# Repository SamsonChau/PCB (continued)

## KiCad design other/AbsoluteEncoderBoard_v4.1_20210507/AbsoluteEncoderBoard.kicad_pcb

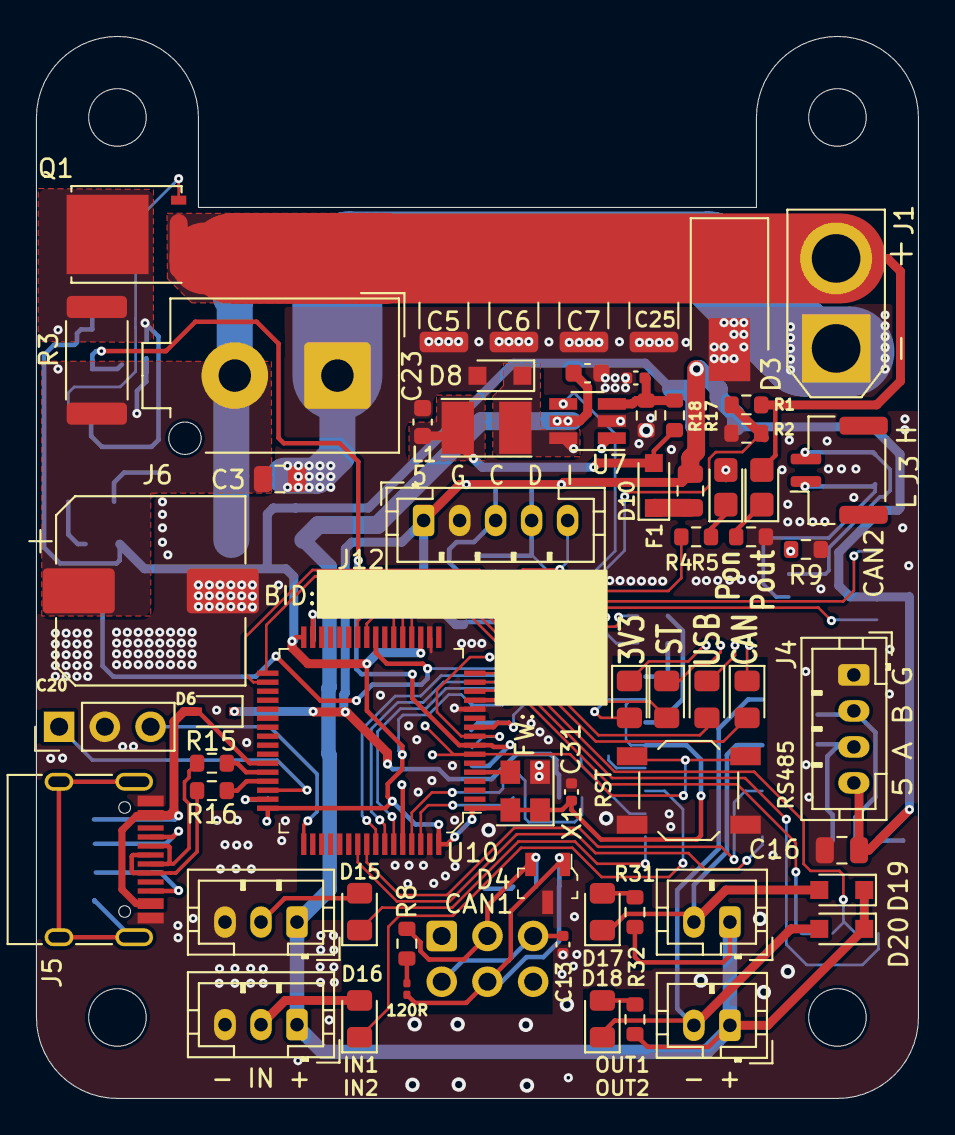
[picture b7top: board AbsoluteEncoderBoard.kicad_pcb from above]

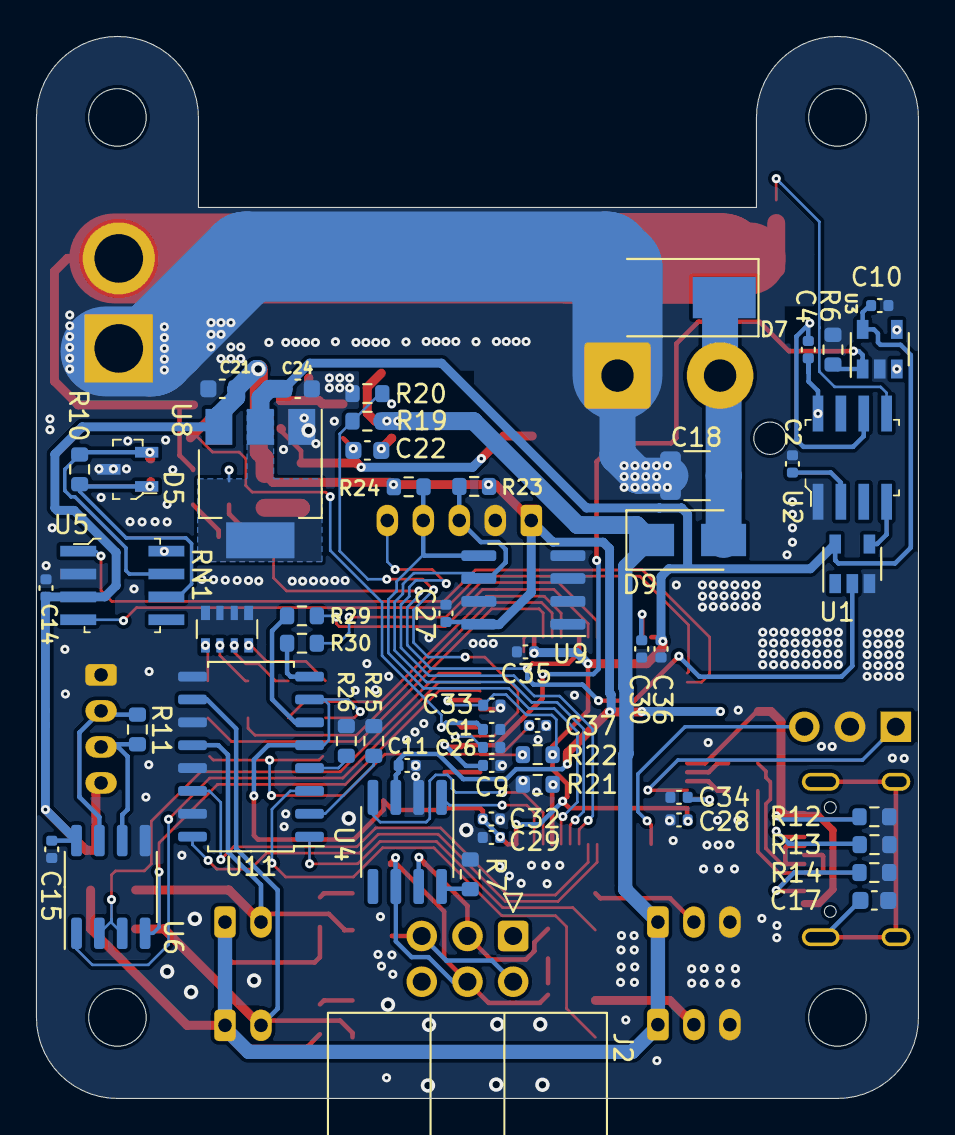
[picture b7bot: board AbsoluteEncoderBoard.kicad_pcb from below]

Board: 2 copper layers, 49.0 x 59.0 mm, 116 parts (55 on the bottom side), 79 nets.

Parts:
C1, C4, C9, C10, C11, C14, C15, C26, C27, C28, C29, C32, C33, C35, C36, C37: .1u; C_0402_1005Metric
C2: 10nF; C_0402_1005Metric
C3: 22u 50V; C_0805_2012Metric
C5, C6, C7, C8: 100u; C_1210_3225Metric
C13, C25: 30p; C_0402_1005Metric
C16: 22u; C_0805_2012Metric
C17: 30p; C_0603_1608Metric
C18: 100uF; C_1210_3225Metric
C19, C23: 10u; C_0603_1608Metric
C20: 330u; CP_Elec_10x10
C21, C24: 1u; C_0603_1608Metric
C22: .1u; C_0603_1608Metric
C30, C34: 2.2u; C_0402_1005Metric
C31: 0.01u; C_0402_1005Metric
D1: G; LED_0805_2012Metric_Castellated
D2: R; LED_0805_2012Metric_Castellated
D3: SMBJ30CA; D_SMB_Handsoldering
D4, D5: PESD1CAN_215; SOT-23-3
D6: N/A; D_SOD-323
D7: SMBJ24CA; D_SMB_Handsoldering
D8, D10, D19, D20: 1N5819; D_SOD-323_HandSoldering
D9: SS24; D_SMA
D11, D15, D16, D17, D18: G; LED_0805_2012Metric_Pad1.15x1.40mm_HandSolder
D12: R; LED_0805_2012Metric_Pad1.15x1.40mm_HandSolder
D13: B; LED_0805_2012Metric_Pad1.15x1.40mm_HandSolder
D14: Y; LED_0805_2012Metric_Pad1.15x1.40mm_HandSolder
F1: .5A; Fuse_0805_2012Metric
J1: XT30-F; AMASS_XT30U-F_1x02_P5.0mm_Vertical
J2: IDC_6P; IDC-Header_2x03_P2.54mm_Horizontal_Lock
J3: JST_GH_2P_HORZ; JST_GH_SM02B-GHS-TB_1x02-1MP_P1.25mm_Horizontal
J4: CONN_04JST-PTH; JST_PH_B4B-PH-K_1x04_P2.00mm_Vertical
J5: USB_C_M12; USB_C_Receptacle_HRO_TYPE-C-31-M-12
J6: MegaFit; Molex_Mega-Fit_76829-0102_2x01_P5.70mm_Vertical
J7: HDR_3P_Hor; PinHeader_1x03_P2.54mm_Vertical
J8, J9: JST_PH3; JST_PH_B3B-PH-K_1x03_P2.00mm_Vertical
J10, J11: JST_PH2; JST_PH_B2B-PH-K_1x02_P2.00mm_Vertical
J12: PH_5P; JST_PH_B5B-PH-K_1x05_P2.00mm_Vertical
L1: 3.3uH; L_Taiyo-Yuden_NR-30xx_HandSoldering
Q1: NVMFS5C450; TDSON-8-1
R1, R19: 27K; R_0603_1608Metric
R2, R4, R7, R9, R21: 2K; R_0603_1608Metric
R3: .002R; R_2512_6332Metric
R5, R12, R18, R22, R23, R24, R25, R26, R31, R32: 22K; R_0603_1608Metric
R6: 330K; R_0603_1608Metric
R8, R10, R11: 120R; R_0603_1608Metric
R13, R14: 5.1K; R_0603_1608Metric
R15, R16: 22R; R_0603_1608Metric
R17: 124K; R_0603_1608Metric
R20: 2K2; R_0603_1608Metric
R27: 0R/NA; R_0201_0603Metric
R29, R30: 100R; R_0603_1608Metric
RN1: 1K; R_Array_Convex_4x0603
SW1: SW_Push; SW_SPST_TL3342
U1: SN74LVC1G14DBV; SOT-23-5
U2: LT1910E; SOIC-8_W3.9mm
U3: INA138; SOT-23-5
U4: MCP2551-I-SN; SOIC-8_3.9x4.9mm_P1.27mm
U5: MCP2551; SOIC-8_W3.9mm
U6: MAX485E; SO-8_3.9x4.9mm_P1.27mm
U7: MP2451; SOT-23-6_Handsoldering
U8: AMS1117-3.3; SOT-223-3_TabPin2
U9: AT24CS64-SSHM; SOIC-8_3.9x4.9mm_P1.27mm
U10: STM32F405RGT6; LQFP-64_10x10mm
U11: TLP291-4; SOIC-16_4.55x10.3mm_P1.27mm
X1: ASE-12MHz; Oscillator_SMD_Abracon_ASE-4Pin_3.2x2.5mm

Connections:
+3V3: C10.1, C24.1, C28.1, C29.1, C31.1, C32.1, C33.1, C35.1, C36.1, D1.2, D11.2, R22.2, U1.5, U3.5, U8.2, U10.1, U10.13, U10.19, U10.32, U10.48, U10.64, U11.5, U11.7, X1.1, X1.4
+5V: C11.1, C14.2, C15.1, C16.1, C21.1, C27.1, D6.1, F1.1, J4.4, J12.1, R23.1, R24.1, U4.3, U5.3, U6.8, U8.3, U9.8
+24V: C19.1, D9.1, D19.1, D20.1, J8.1, J9.1, J10.1, J11.1, R19.2, R31.1, R32.1, U7.5
+BATT: C3.1, C4.1, C18.1, C20.1, D7.1, D9.2, J6.2, R3.1, U2.8, U3.3
/CAN1/CANH: D4.2, J2.3, R8.1, U4.7
/CAN1/CANL: D4.1, J2.4, R27.2, U4.6
/CAN1/SH: C13.1, J2.2, J2.5
/CAN1_RX: U4.4, U10.61
/CAN1_TX: U4.1, U10.62
/CAN2/CAN+: D5.2, J3.2, R10.1, U5.7
/CAN2/CAN-: D5.1, J3.1, R10.2, U5.6
/CAN2_RX: U5.4, U10.33
/CAN2_TX: U5.1, U10.34
/IN1: U10.55, U11.16
/IN2: U10.56, U11.14
/I_SEN: C9.1, R6.2, U3.1, U10.8
/MCU/BOOT0: R21.2, U10.60
/MCU/I2C1_INT: J12.5, U10.57
/MCU/LED1: D12.2, U10.22
/MCU/LED2: D13.2, U10.21
/MCU/LED3: D14.2, U10.20
/MCU/NRST: C37.2, R22.1, SW1.2, U10.7
/MCU/RCC_OSC_IN: U10.5, X1.3
/MCU/SYS_SWCLK: J7.3, U10.49
/MCU/SYS_SWDIO: J7.1, U10.46
/MCU/USB_DM: R15.1, U10.44
/MCU/USB_DP: R16.1, U10.45
/MCU/VCAP1: C30.1, U10.31
/MCU/VCAP2: C34.1, U10.47
/OUT1: R29.2, U10.25
/OUT2: R30.2, U10.26
/PWR_ON: R4.1, U1.2, U10.24
/RS485/RS485_N: J4.2, R11.2, U6.7
/RS485/RS485_P: J4.3, R11.1, U6.6
/RS485_RX: U6.1, U10.15
/RS485_TX: U6.4, U10.14
/RS485_TXEN: U6.2, U6.3, U10.16
/SCL: J12.3, R23.2, U9.6, U10.58
/SDA: J12.4, R24.2, U9.5, U10.59
/USB/USBD+: J5.A6, J5.B6, R16.2
/USB/USBD-: J5.A7, J5.B7, R15.2
/USB/VBUS: D6.2, J5.A4, J5.A9, J5.B4, J5.B9, R12.1, U10.43
/VIN_SEN: C26.1, R19.1, R20.2, U7.4, U10.9
/VOUT_SEN: C1.1, R1.1, R2.2, U10.10
/VoltageReg/FB: C25.2, R17.1, R18.2, U7.3
/dji_power/GATE: Q1.4, U2.5
/dji_power/I_SENSE-: C4.2, Q1.5, R3.2, U2.6, U3.4
/dji_power/M_ON: U1.4, U2.4
GND: C1.2, C2.2, C3.2, C5.2, C6.2, C7.2, C8.2, C9.2, C10.2, C11.2, C13.2, C14.1, C15.2, C16.2, C17.1, C18.2, C19.2, C20.2, C21.2, C23.1, C24.2, C25.1, C26.2, C27.2, C28.2, C29.2, C30.2, C31.2, C32.2, C33.2, C34.2, C35.2, C36.2, C37.1, D3.2, D4.3, D5.3, D7.2, D8.2, J1.1, J4.1, J5.A1, J5.A12, J5.B1, J5.B12, J6.1, J7.2, J8.3, J9.3, J12.2, R2.1, R5.1, R6.1, R7.1, R9.1, R12.2, R13.1, R14.1, R18.1, R20.1, R21.1, R25.2, R26.2, RN1.1, RN1.2, RN1.3, RN1.4, SW1.1, U1.3, U2.1, U3.2, U4.2, U5.2, U6.5, U7.2, U8.1, U9.1, U9.2, U9.3, U9.4, U9.7, U10.12, U10.18, U10.63, U11.9, U11.11, U11.13, U11.15, X1.2
unnamed: C2.1, U2.2
unnamed: C17.2, J5.S1
unnamed: C22.1, D8.1, L1.1, U7.6
unnamed: C22.2, U7.1
unnamed: C23.2, D10.2, L1.2, R17.2
unnamed: D1.1, R4.2
unnamed: D2.1, R5.2
unnamed: D10.1, F1.2
unnamed: D11.1, RN1.8
unnamed: D12.1, RN1.7
unnamed: D13.1, RN1.6
unnamed: D14.1, RN1.5
unnamed: D15.1, U11.1
unnamed: D15.2, J8.2
unnamed: D16.1, U11.3
unnamed: D16.2, J9.2
unnamed: D17.1, D19.2, J10.2, U11.12
unnamed: D17.2, R31.2
unnamed: D18.1, D20.2, J11.2, U11.10
unnamed: D18.2, R32.2
unnamed: J5.A5, R13.2
unnamed: J5.B5, R14.2
unnamed: R7.2, U4.8
unnamed: R9.2, U5.8
unnamed: R25.1, U11.2
unnamed: R26.1, U11.4
unnamed: R8.2, R27.1
unnamed: R29.1, U11.6
unnamed: R30.1, U11.8
Vdrive: C5.1, C6.1, C7.1, C8.1, D2.2, D3.1, J1.2, Q1.1, Q1.2, Q1.3, R1.2

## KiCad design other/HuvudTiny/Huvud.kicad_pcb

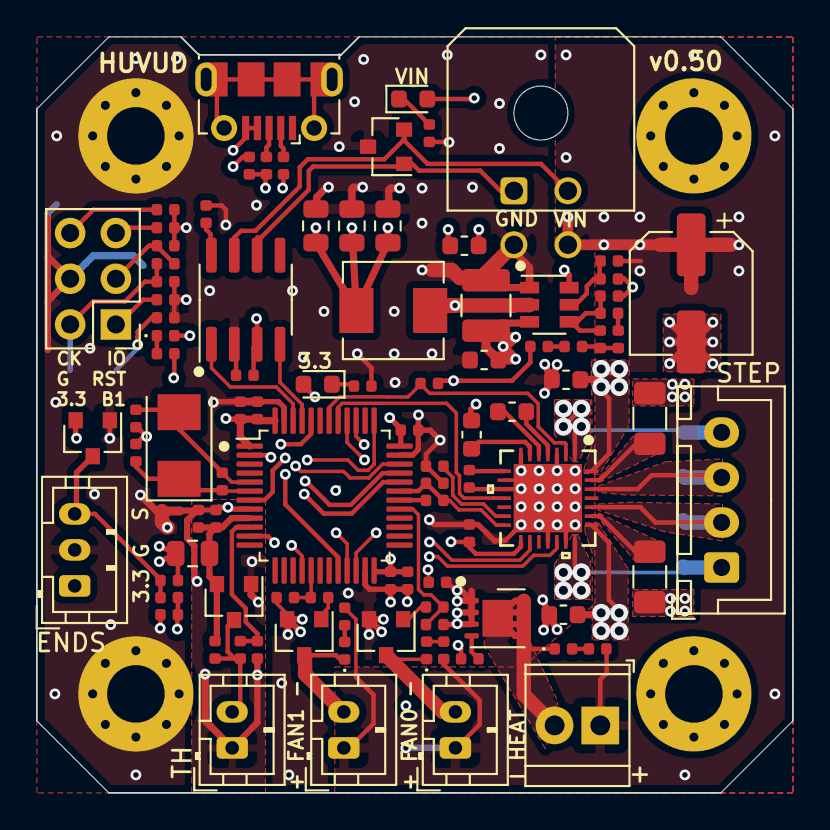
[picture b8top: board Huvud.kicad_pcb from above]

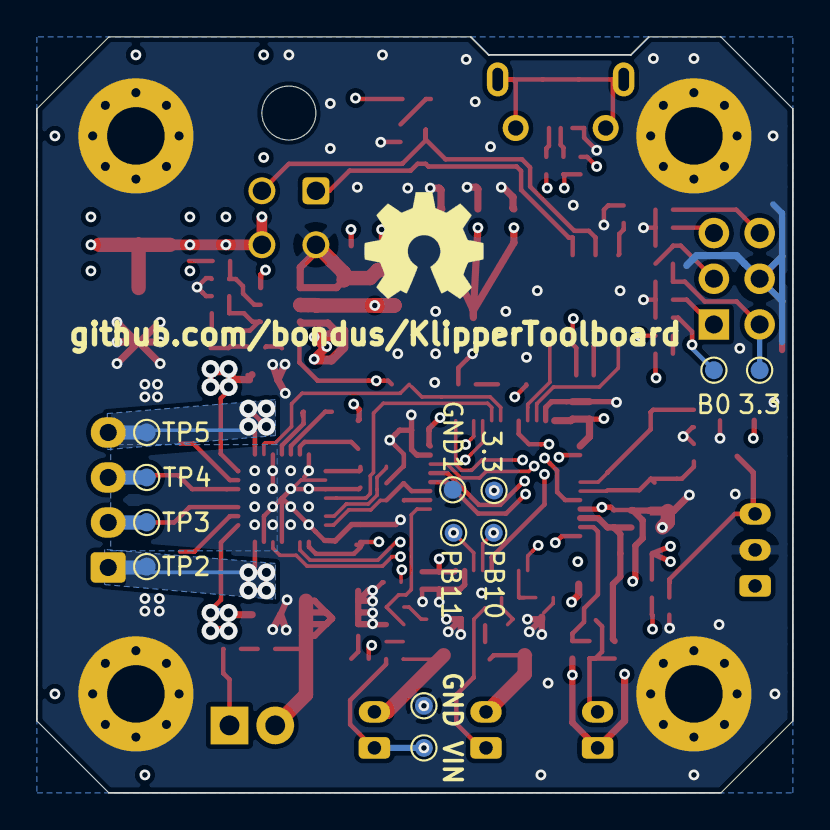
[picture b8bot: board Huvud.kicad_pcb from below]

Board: 4 copper layers, 42.0 x 42.0 mm, 113 parts (13 on the bottom side), 67 nets.

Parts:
3.3: TestPoint; TestPoint_Pad_D1.0mm
C1, C4, C23, C27: 4.7uF; C_0402_1005Metric
C2, C9, C10, C11, C17, C18, C19, C24, C25, C28: 0.1uF; C_0402_1005Metric
C3, C6, C7, C16, C20: 0.1uF/35V; C_0603_1608Metric
C5: 22nf/50V; C_0603_1608Metric
C8: 100uF/35V; CP_Elec_6.3x5.8
C12, C13: 22pF; C_0402_1005Metric
C14, C15, C32: 10uF; C_0805_2012Metric
C21: 68pF; C_0402_1005Metric
C22: 10uF/35V; C_1210_3225Metric
D1, D2, D3, D5: LEDGR; LED_0402_1005Metric
D4, D9: BAT54S; SOT-23
D6, D8: LEDRED; LED_0603_1608Metric
D7: SM24CANB; SOT-23
GND1, GND2: TestPoint; TestPoint_Pad_D1.0mm
H1, H2, H3, H4: MountingHole; MountingHole_3.2mm_M3_Pad_Via
J1: Conn_02x02_Odd_Even; Molex_Micro-Fit_3.0_43045-0400_2x02_P3.00mm_Horizontal
J2: DBG; PinHeader_2x03_P2.54mm_Vertical
J3: THERM; JST_PH_B2B-PH-K_1x02_P2.00mm_Vertical
J4: FAN0; JST_PH_B2B-PH-K_1x02_P2.00mm_Vertical
J5: FAN1; JST_PH_B2B-PH-K_1x02_P2.00mm_Vertical
J6: Heater; TerminalBlock_TE_282834-2_1x02_P2.54mm_Horizontal
J7: Endstop; JST_PH_B3B-PH-K_1x03_P2.00mm_Vertical
J9: STEPPER; JST_XH_B4B-XH-A_1x04_P2.50mm_Vertical
J12: USB_Micro-B_Molex-105017-0001
L1: 22uH; L_0805_2012Metric
L4: 10uH/max 145mOhm 2A; L_Sunlord_MWSA0518_5.4x5.2mm
LOGO1: Logo_Open_Hardware_Small; OSHW-Symbol_6.7x6mm_SilkScreen
NT1: Net-Tie_2; NetTie-2_SMD_Pad0.5mm
PB10, PB11: TestPoint; TestPoint_Pad_D1.0mm
Q1, Q2: AO3400A; SOT-23
Q3: AON7524; DFN-8-1EP_3x3mm_P0.65mm_EP1.7x2.05mm
R1: 4.7k; R_0402_1005Metric
R2, R27, R29: 2.2k; R_0402_1005Metric
R3, R20: 470; R_0402_1005Metric
R4, R7: 0.110 1%; R_1206_3216Metric
R5, R8, R10, R11, R12, R13, R14, R15, R19, R21, R22, R23, R36, R37: 10k; R_0402_1005Metric
R6, R16: 1k; R_0402_1005Metric
R9: 1M; R_0402_1005Metric
R17, R18, R24, R39, R41: 22k; R_0402_1005Metric
R25, R26, R28, R30, R31, R34, R35: 22; R_0402_1005Metric
R38, R40: 100k; R_0402_1005Metric
TP1, TP2, TP3, TP4, TP5, TP6: TestPoint; TestPoint_Pad_D1.0mm
U2: TMC2209-LA
U3: TPS54308; SOT-23-6
U5: STM32F103C8T6; LQFP-48_7x7mm_P0.5mm
U6: SN65HVD230; SOIC-8_3.9x4.9mm_P1.27mm
VIN1: TestPoint; TestPoint_Pad_D1.0mm
Y1: 8Mhz; Crystal_SMD_5032-2Pin_5.0x3.2mm

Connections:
+3V3: 3.3.1, C1.1, C9.2, C10.1, C14.1, C15.1, C17.1, C18.1, C24.1, C27.1, C28.2, C32.1, D4.2, D5.2, D8.2, J2.2, J7.1, L1.1, L4.2, R1.1, R18.1, R19.2, R27.2, R30.1, TP6.1, U2.15, U5.1, U5.24, U5.36, U5.48, U6.3
/ST_A1: J9.2, TP3.1, U2.24
/ST_A2: J9.1, TP2.1, U2.21
/ST_B1: J9.3, TP4.1, U2.26
/ST_B2: J9.4, TP5.1, U2.1
AREF: C11.2, C23.2, D9.2, L1.2, R2.2, U5.9
BOOT0: R23.2, TP1.1, U5.44
BOOT1: J2.1, R37.2, U5.20
BRA: R4.2, U2.23
BRB: R7.2, U2.27
CANH: D7.2, J1.2, U6.7
CANL: D7.1, J1.1, U6.6
CANRX: U5.45, U6.4
CANTX: U5.46, U6.1
ENDSTOP: C2.1, R36.2, U5.11
FAN0: R8.2, R34.1, U5.29
FAN1: R10.2, R35.1, U5.17
GND: C1.2, C2.2, C4.2, C6.2, C7.2, C8.2, C9.1, C10.2, C12.1, C13.1, C14.2, C15.2, C16.2, C17.2, C18.2, C19.1, C22.1, C24.2, C27.2, C28.1, C32.2, D4.1, D7.3, GND1.1, GND2.1, H1.1, H2.1, H3.1, H4.1, J1.3, J2.4, J7.2, J12.4, J12.5, NT1.1, Q1.2, Q2.2, Q3.1, R4.1, R6.2, R7.1, R8.1, R10.1, R11.2, R12.1, R17.2, R20.2, R21.1, R22.2, R23.1, R24.1, R37.1, R39.1, R41.1, U2.3, U2.7, U2.9, U2.10, U2.18, U2.20, U2.29, U3.1, U5.23, U5.35, U5.47, U6.2
GNDA: C11.1, C23.1, C25.1, D9.1, J3.1, NT1.2, U5.8
HEATER: R12.2, R28.1, U5.16
LED0: R3.1, U5.2
NRST: C19.2, J2.3, R1.2, U5.7
unnamed: C3.1, U2.6
unnamed: C4.1, U2.8
unnamed: C5.1, U2.5
unnamed: C5.2, U2.4
unnamed: C12.2, R9.1, U5.6, Y1.1
unnamed: C13.2, R9.2, U5.5, Y1.2
unnamed: C20.1, L4.1, U3.2
unnamed: C20.2, U3.6
unnamed: C21.1, R40.1, R41.2, U3.4
unnamed: C21.2, R29.1
unnamed: D1.1, J4.2, Q1.3
unnamed: D1.2, R13.2
unnamed: D2.1, J5.2, Q2.3
unnamed: D2.2, R14.2
unnamed: D3.1, J6.2, Q3.3
unnamed: D3.2, R15.2
unnamed: D4.3, J7.3, R19.1, R36.1
unnamed: D5.1, R3.2
unnamed: D6.1, R11.1
unnamed: D8.1, R20.1
unnamed: D9.3, J3.2, R2.1, R5.2
unnamed: J12.2, R26.2
unnamed: J12.3, R25.2
unnamed: PB10.1, U5.21
unnamed: PB11.1, U5.22
unnamed: Q1.1, R34.2
unnamed: Q2.1, R35.2
unnamed: Q3.2, R28.2
unnamed: R6.1, U6.8
unnamed: R17.1, U2.13
unnamed: R29.2, R31.1, R40.2
unnamed: R30.2, R31.2
unnamed: R38.1, R39.2, U3.5
ST_DIAG: U2.11, U5.41
ST_DIR: U2.19, U5.40
ST_EN: R18.2, U2.2, U5.42
ST_STEP: U2.16, U5.39
ST_UART_RX: R16.2, R24.2, U2.14, U5.31
ST_UART_TX: R16.1, U5.30
ST_VS: C3.2, C6.1, C7.1, C8.1, C16.1, C22.2, D6.2, J1.4, J4.1, J5.1, J6.1, R13.1, R14.1, R15.1, R38.2, U2.22, U2.28, U3.3, VIN1.1
SWCLK: J2.6, R21.2, U5.37
SWDIO: J2.5, R22.1, U5.34
THERM: C25.2, R5.1, U5.10
USBDM: R26.1, U5.32
USBDP: R25.1, R27.1, U5.33
